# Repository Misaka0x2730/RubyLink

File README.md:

# RubyLink
Hardware platform for Miyako-Link based on RP2040

Firmware: https://github.com/Misaka0x2730/Miyako-Link

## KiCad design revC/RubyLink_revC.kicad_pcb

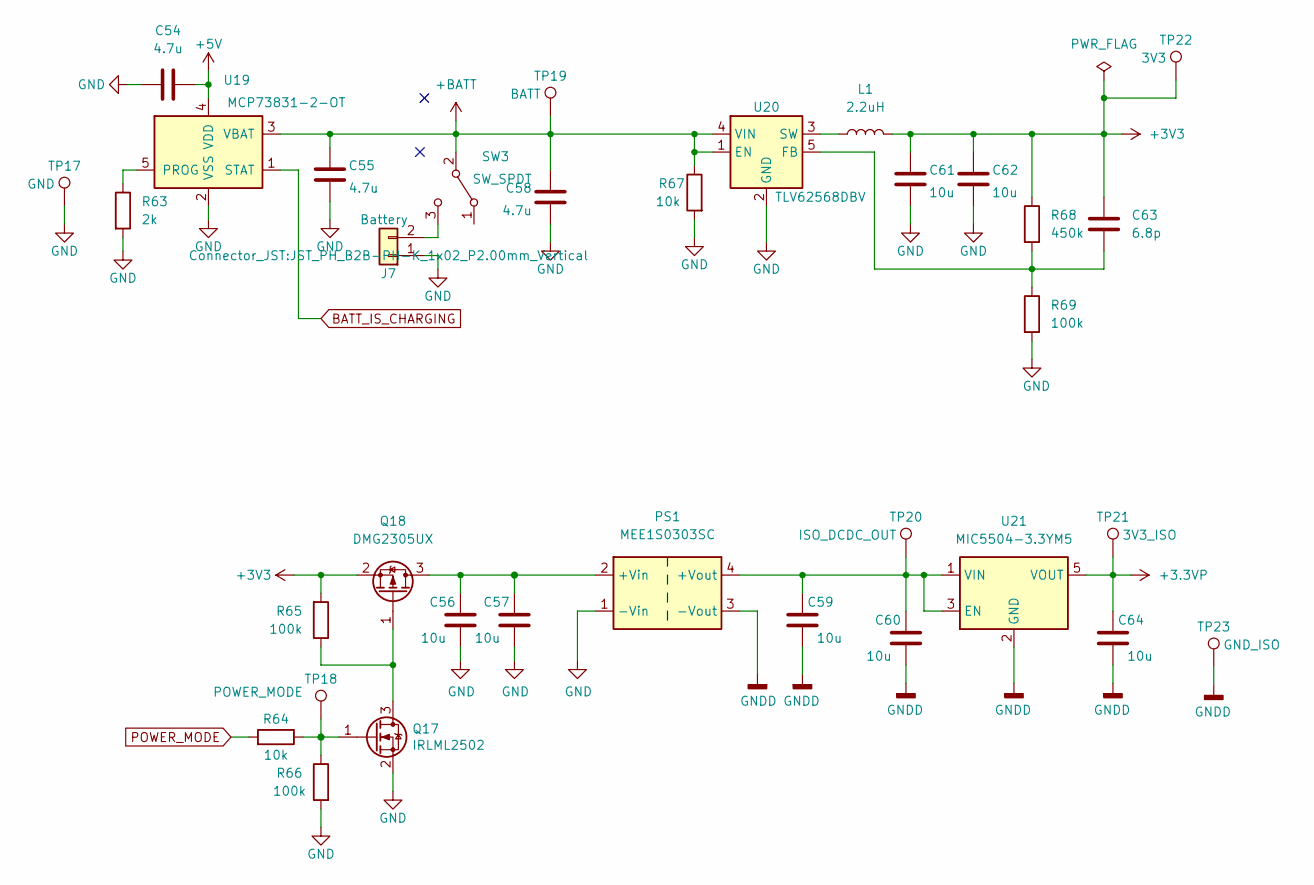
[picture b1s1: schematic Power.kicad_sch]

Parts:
C54, C55, C58: 4.7u; C_0603_1608Metric
C56, C57, C59, C60, C64: 10u; C_0603_1608Metric; Part Number CC0603KRX5R6BB106
C61, C62: 10u; C_0603_1608Metric
C63: 6.8p; C_0402_1005Metric
J7: Battery; JST_PH_B2B-PH-K_1x02_P2.00mm_Vertical
L1: 2.2uH; L_Taiyo-Yuden_NR-30xx; Part number NR3012T2R2M
PS1: MEE1S0303SC; Converter_DCDC_Murata_MEE1SxxxxSC_THT
Q17: IRLML2502; SOT-23; Part Number IRLML2502TRPBF
Q18: DMG2305UX; SOT-23
R63: 2k; R_0402_1005Metric
R64, R67: 10k; R_0402_1005Metric
R65, R69: 100k; R_0402_1005Metric
R66: 100k; R_0402_1005Metric; Part Number RC0402FR-0710KL
R68: 450k; R_0402_1005Metric
SW3: SW_SPDT; SW_CuK_OS102011MA1QN1_SPDT_Angled
TP17: GND; TestPoint_Pad_D1.0mm
TP18: POWER_MODE; TestPoint_Pad_D1.0mm
TP19: BATT; TestPoint_Pad_D1.0mm
TP20: ISO_DCDC_OUT; TestPoint_Pad_D1.0mm
TP21: 3V3_ISO; TestPoint_Pad_D1.0mm
TP22: 3V3; TestPoint_Pad_D1.0mm
TP23: GND_ISO; TestPoint_Pad_D1.0mm
U19: MCP73831-2-OT; SOT-23-5
U20: TLV62568DBV; SOT-23-5
U21: MIC5504-3.3YM5; SOT-23-5

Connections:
+3.3VP: C64.1, TP21.1, U21.5 (VOUT); also elsewhere on the board
+3V3: C61.1, C62.1, C63.1, L1.2, Q18.2 (S), R65.2, R68.1, TP22.1; also elsewhere on the board
+5V: C54.1, U19.4 (VDD); also elsewhere on the board
+BATT: C55.2, C58.2, R67.1, SW3.2 (B), TP19.1, U19.3 (VBAT), U20.1 (EN), U20.4 (VIN)
BATT_IS_CHARGING: U19.1 (STAT); also elsewhere on the board
GND: C54.2, C55.1, C56.2, C57.2, C58.1, C61.2, C62.2, J7.1, PS1.1 (-Vin), Q17.2 (S), R63.2, R66.2, R67.2, R69.2, TP17.1, U19.2 (VSS), U20.2 (GND); also elsewhere on the board
GNDD: C59.2, C60.2, C64.2, PS1.3 (-Vout), TP23.1, U21.2 (GND); also elsewhere on the board
unnamed: C56.1, C57.1, PS1.2 (+Vin), Q18.3 (D)
unnamed: C59.1, C60.1, PS1.4 (+Vout), TP20.1, U21.1 (VIN), U21.3 (EN)
unnamed: C63.2, R68.2, R69.1, U20.5 (FB)
unnamed: J7.2, SW3.3 (C)
unnamed: L1.1, U20.3 (SW)
unnamed: Q17.1 (G), R64.1, R66.1, TP18.1
unnamed: Q17.3 (D), Q18.1 (G), R65.1
unnamed: R63.1, U19.5 (PROG)
POWER_MODE: R64.2; also elsewhere on the board

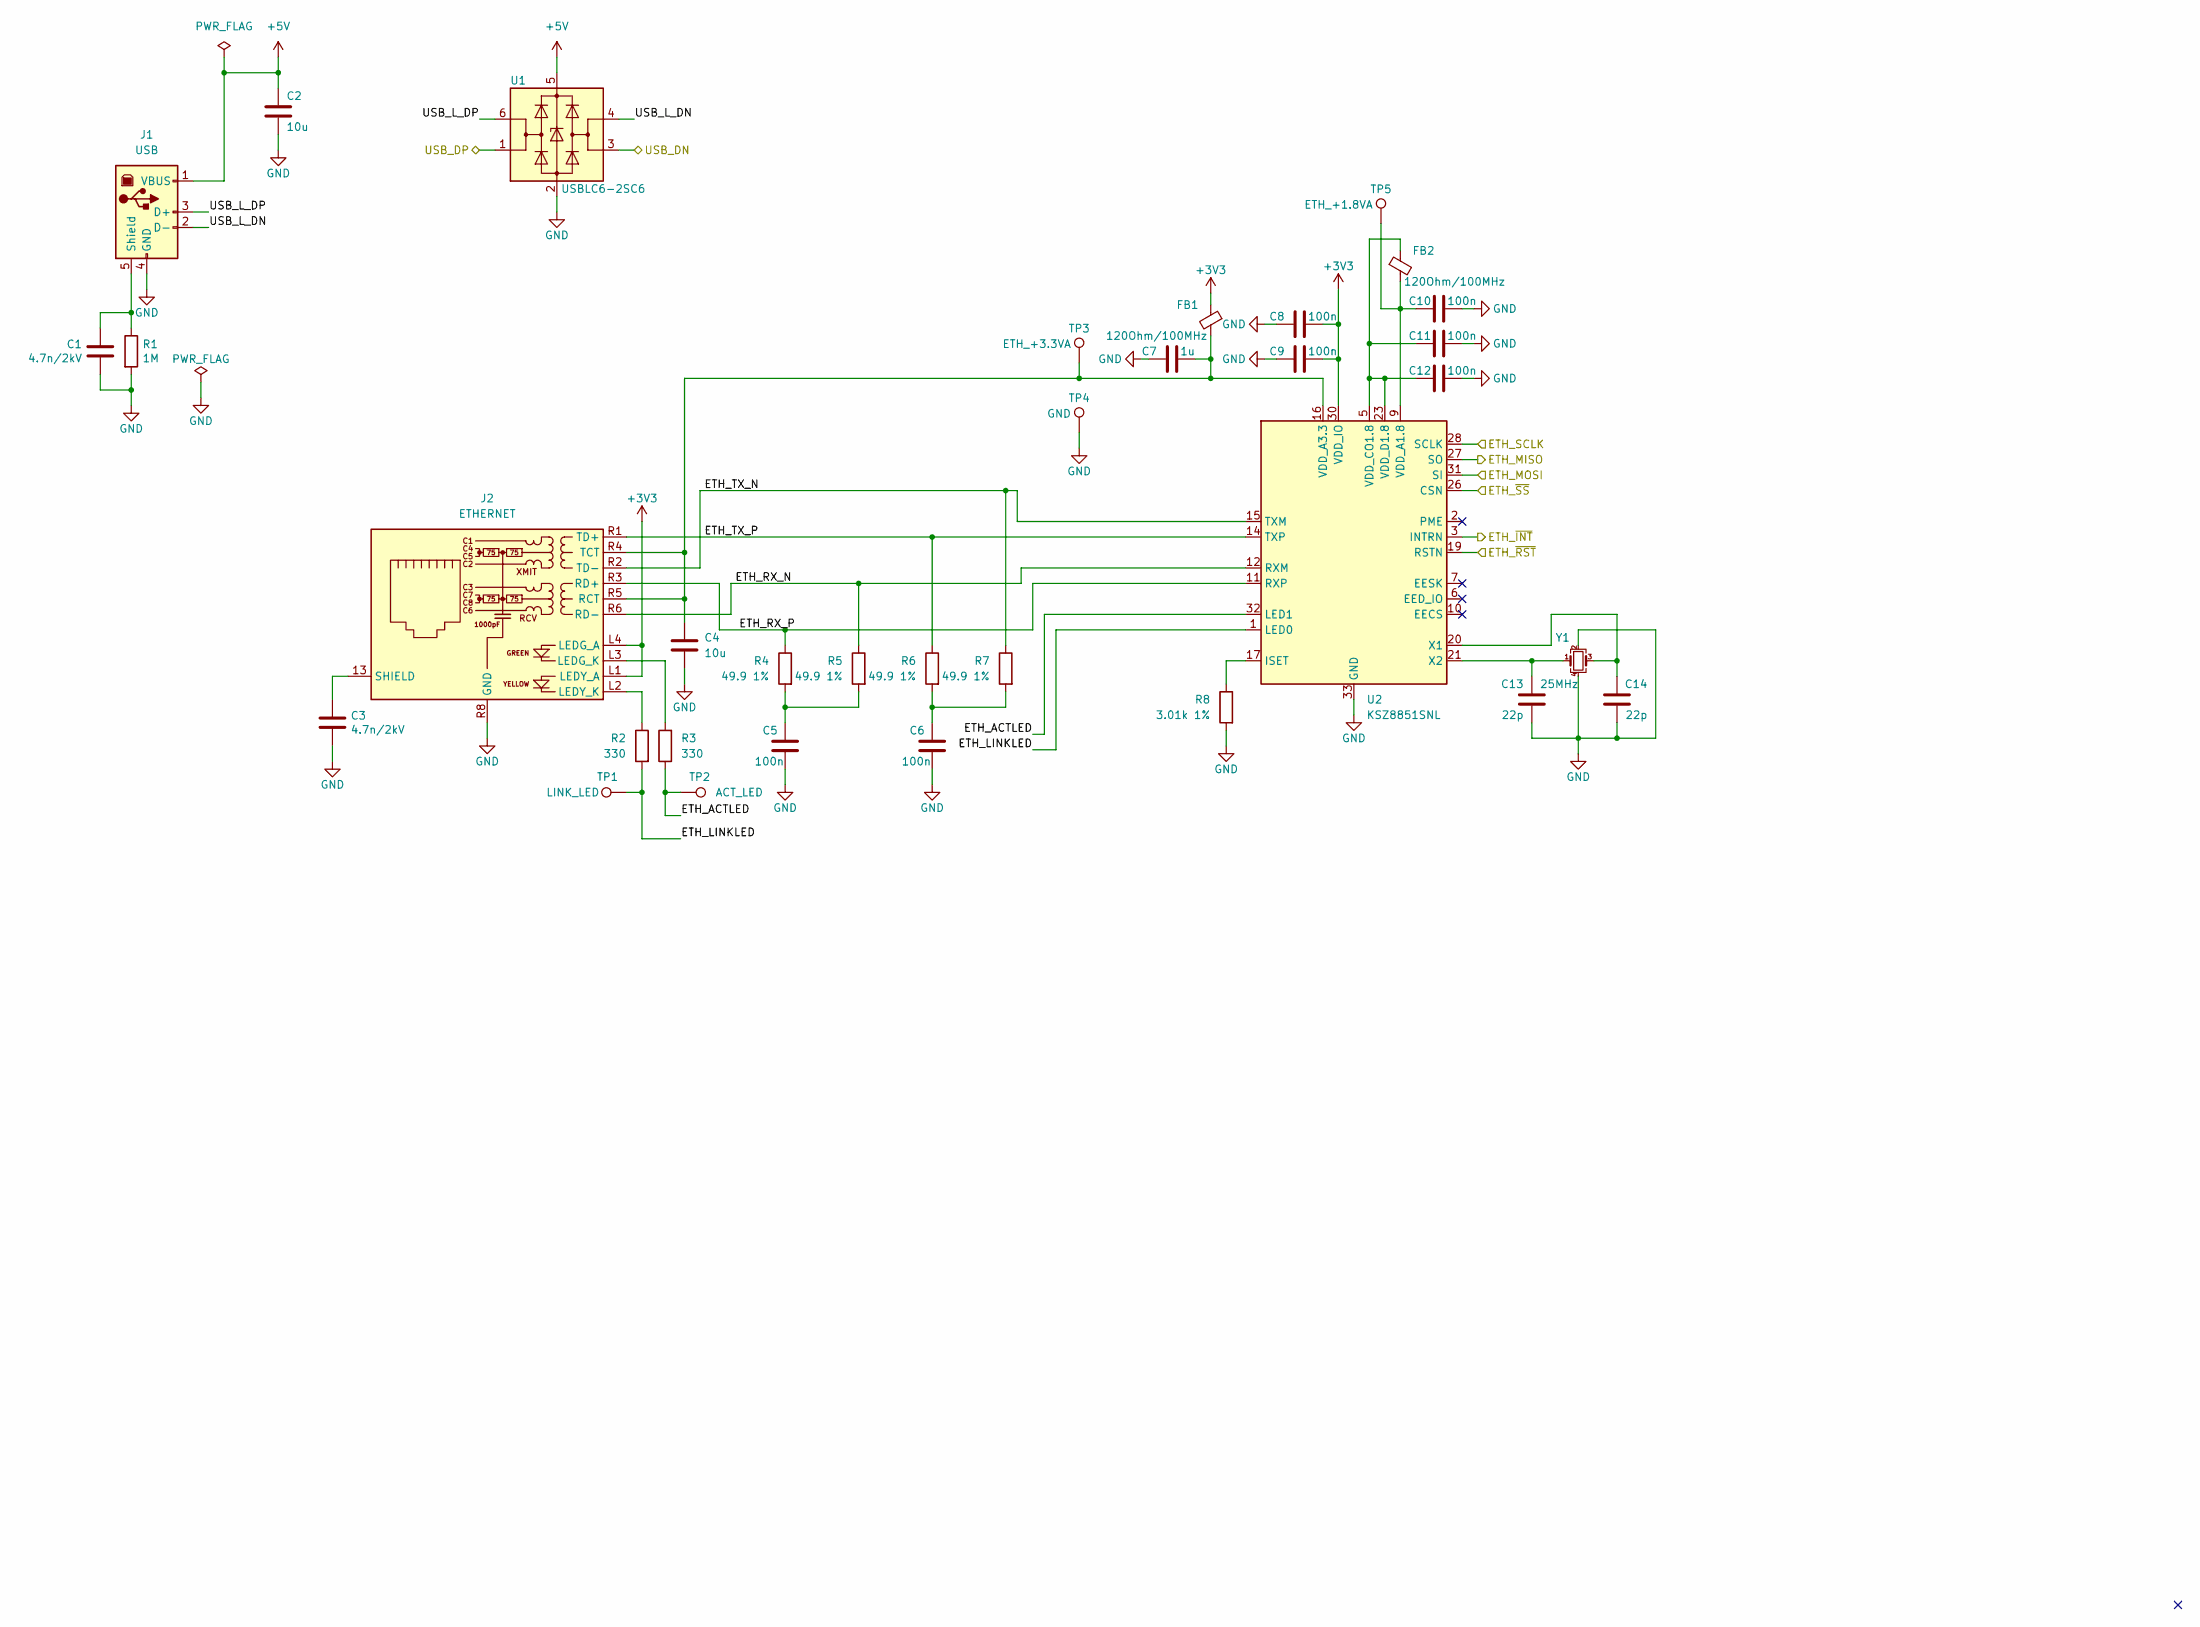
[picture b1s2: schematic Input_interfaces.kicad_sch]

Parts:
C1, C3: 4.7n/2kV; C_1812_4532Metric; Part Number 202S43W472KV4E
C2, C4: 10u; C_0603_1608Metric
C5, C6, C8, C9, C10, C11, C12: 100n; C_0402_1005Metric
C7: 1u; C_0402_1005Metric
C13, C14: 22p; C_0402_1005Metric
FB1, FB2: 120Ohm/100MHz; L_0805_2012Metric
J1: USB; TE_292304-2
J2: ETHERNET; RJ45_Amphenol_RJMG1BD3B8K1ANR
R1: 1M; R_1206_3216Metric; Part Number 1206W4J0105T5E
R2, R3: 330; R_0402_1005Metric
R4, R5, R6, R7: 49.9 1%; R_0603_1608Metric
R8: 3.01k 1%; R_0402_1005Metric
TP1: LINK_LED; TestPoint_Pad_D1.0mm
TP2: ACT_LED; TestPoint_Pad_D1.0mm
TP3: ETH_+3.3VA; TestPoint_Pad_D1.0mm
TP4: GND; TestPoint_Pad_D1.0mm
TP5: ETH_+1.8VA; TestPoint_Pad_D1.0mm
U1: USBLC6-2SC6; SOT-23-6
U2: KSZ8851SNL; TQFN-32-1EP_5x5mm_P0.5mm_EP3.4x3.4mm_ThermalVias
Y1: 25MHz; Crystal_SMD_3225-4Pin_3.2x2.5mm

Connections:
+3V3: C8.2, C9.2, FB1.1, J2.L1 (LEDY_A), J2.L4 (LEDG_A), U2.25 (VDD_IO), U2.30 (VDD_IO); also elsewhere on the board
+5V: C2.1, J1.1 (VBUS), U1.5 (VBUS); also elsewhere on the board
/Input interfaces/ETH_ACTLED: R3.1, TP2.1, U2.32 (LED1)
/Input interfaces/ETH_LINKLED: R2.2, TP1.1, U2.1 (LED0)
/Input interfaces/ETH_MISO: U2.27 (SO); also elsewhere on the board
/Input interfaces/ETH_MOSI: U2.31 (SI); also elsewhere on the board
/Input interfaces/ETH_RX_N: J2.R6 (RD-), R5.1, U2.12 (RXM)
/Input interfaces/ETH_RX_P: J2.R3 (RD+), R4.1, U2.11 (RXP)
/Input interfaces/ETH_SCLK: U2.28 (SCLK); also elsewhere on the board
/Input interfaces/ETH_TX_N: J2.R2 (TD-), R7.1, U2.15 (TXM)
/Input interfaces/ETH_TX_P: J2.R1 (TD+), R6.1, U2.14 (TXP)
/Input interfaces/ETH_~INT: U2.3 (INTRN); also elsewhere on the board
/Input interfaces/ETH_~RST: U2.19 (RSTN); also elsewhere on the board
/Input interfaces/ETH_~SS: U2.26 (CSN); also elsewhere on the board
/Input interfaces/USB_DN: U1.3 (I/O2); also elsewhere on the board
/Input interfaces/USB_DP: U1.1 (I/O1); also elsewhere on the board
/Input interfaces/USB_L_DN: J1.2 (D-), U1.4 (I/O2)
/Input interfaces/USB_L_DP: J1.3 (D+), U1.6 (I/O1)
GND: C1.1, C2.2, C3.1, C4.1, C5.2, C6.2, C7.1, C8.1, C9.1, C10.2, C11.2, C12.2, C13.2, C14.2, J1.4 (GND), J2.R8 (GND), R1.2, R8.2, TP4.1, U1.2 (GND), U2.4 (DGND), U2.8 (AGND), U2.13 (AGND), U2.18 (AGND), U2.22 (DGND), U2.24 (DGND), U2.29 (DGND), U2.33 (GND), Y1.2, Y1.4; also elsewhere on the board
unnamed: C1.2, J1.5 (Shield), R1.1
unnamed: C3.2, J2.13 (SHIELD)
unnamed: C4.2, C7.2, FB1.2, J2.R4 (TCT), J2.R5 (RCT), TP3.1, U2.16 (VDD_A3.3)
unnamed: C5.1, R4.2, R5.2
unnamed: C6.1, R6.2, R7.2
unnamed: C10.1, FB2.2, TP5.1, U2.9 (VDD_A1.8)
unnamed: C11.1, C12.1, FB2.1, U2.5 (VDD_CO1.8), U2.23 (VDD_D1.8)
unnamed: C13.1, U2.21 (X2), Y1.1
unnamed: C14.1, U2.20 (X1), Y1.3
unnamed: J2.L2 (LEDY_K), R2.1
unnamed: J2.L3 (LEDG_K), R3.2
unnamed: R8.1, U2.17 (ISET)

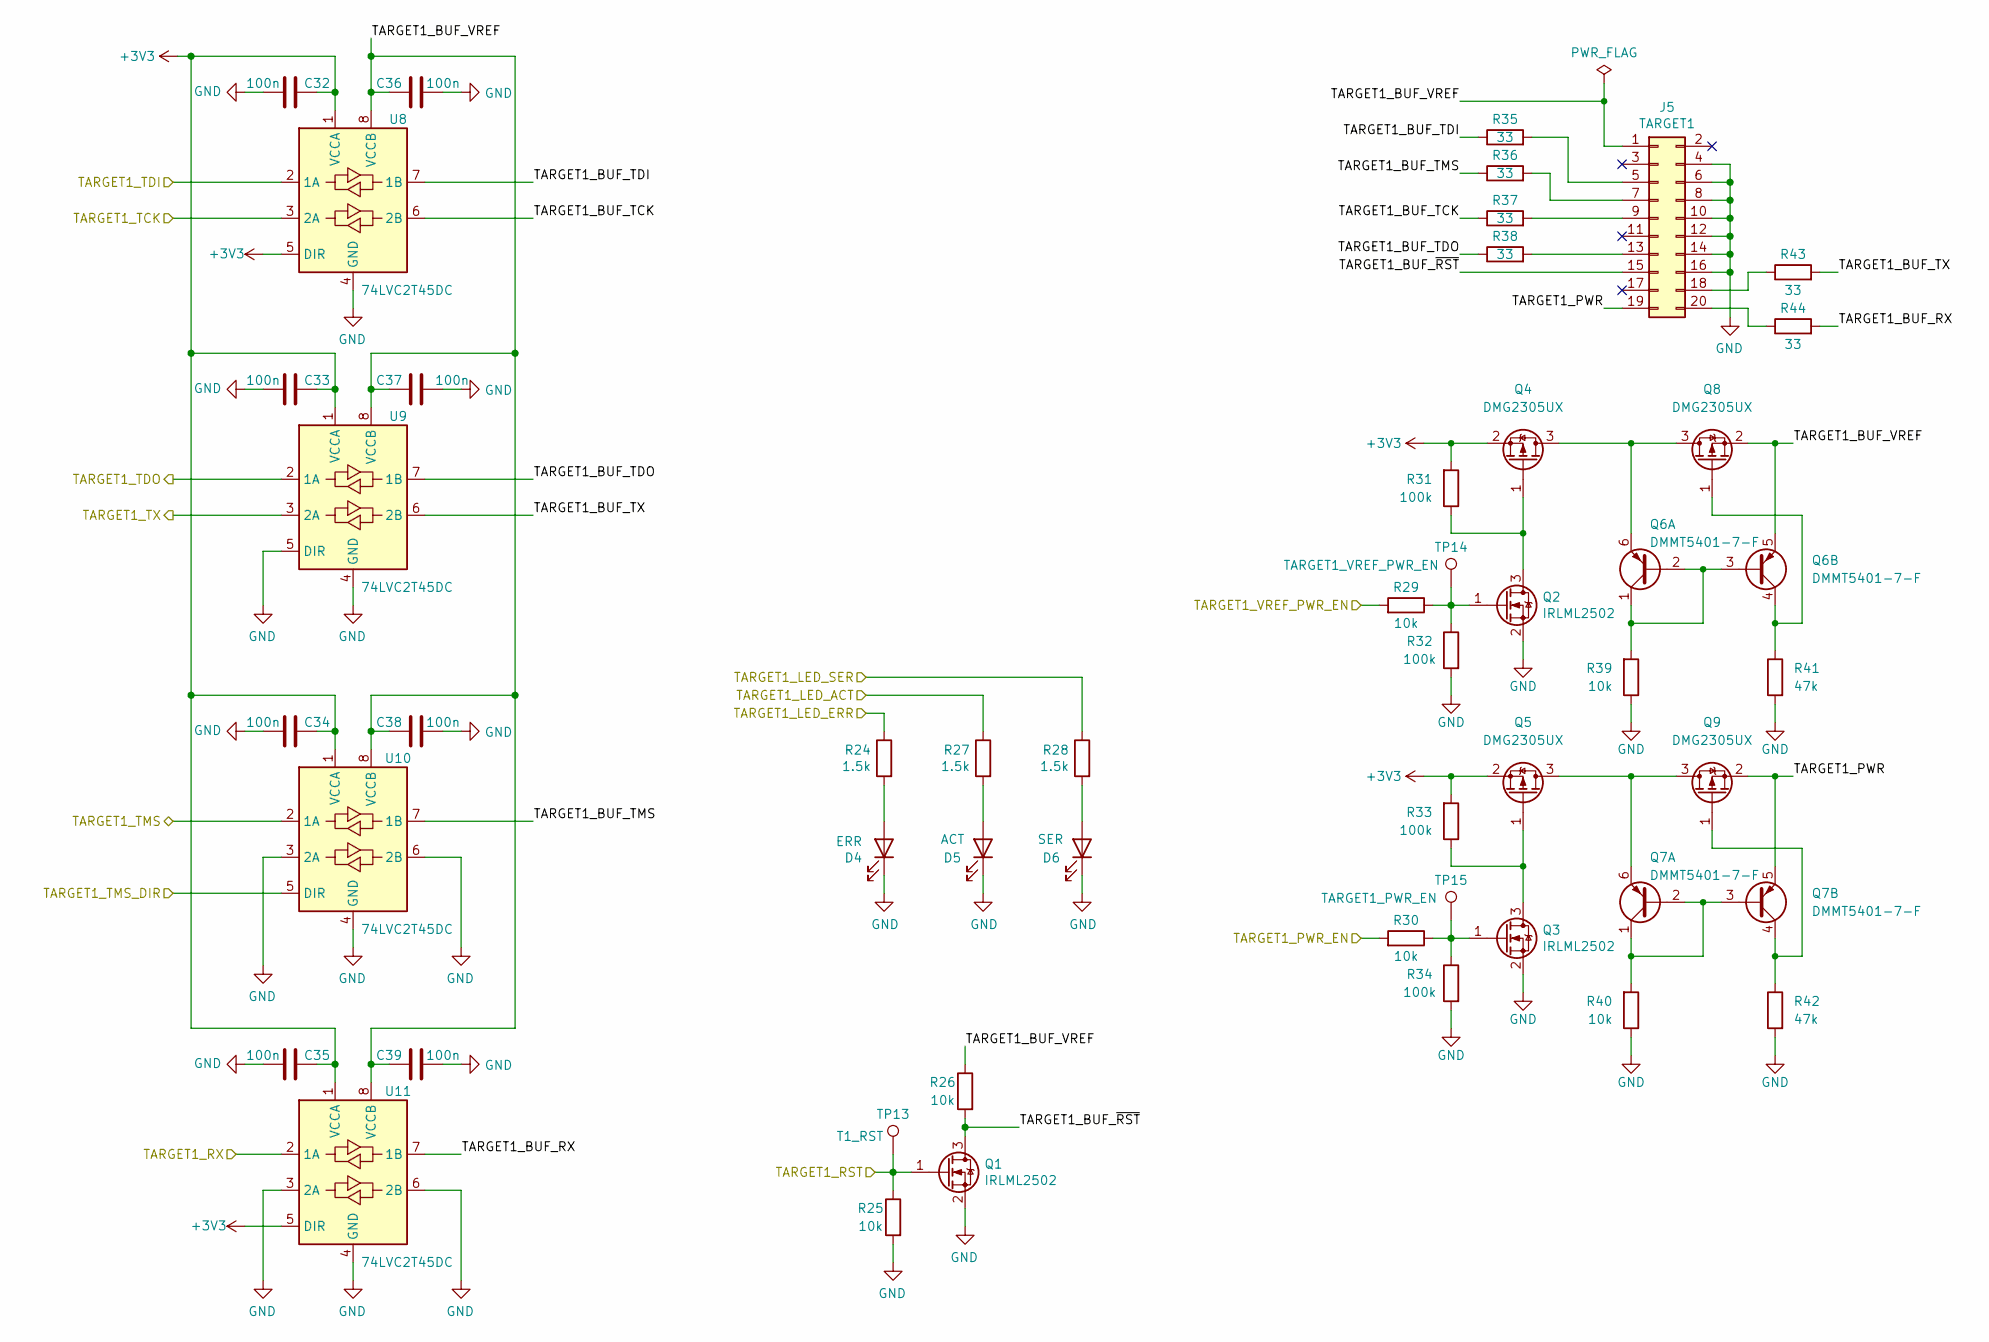
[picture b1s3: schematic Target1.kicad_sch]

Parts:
C32, C33, C34, C35, C36, C37, C38, C39: 100n; C_0402_1005Metric; Part Number CC0402KRX7R7BB104
D4: ERR; LED_D3.0mm
D5: ACT; LED_D3.0mm
D6: SER; LED_D3.0mm; Part Number FYLS-0603UYC
J5: TARGET1; IDC-Header_2x10_P2.54mm_Horizontal; Part Number BH-20R
Q1, Q2, Q3: IRLML2502; SOT-23; Part Number IRLML2502TRPBF
Q4, Q5, Q8, Q9: DMG2305UX; SOT-23
Q6, Q7: DMMT5401-7-F; SOT-23-6
R24, R27, R28: 1.5k; R_0603_1608Metric; Part Number RC0402FR-071K5L
R25, R26: 10k; R_0402_1005Metric; Part Number RC0402FR-0710KL
R29, R30, R39, R40: 10k; R_0402_1005Metric
R31, R33: 100k; R_0402_1005Metric
R32, R34: 100k; R_0402_1005Metric; Part Number RC0402FR-0710KL
R35, R36, R37, R38, R43, R44: 33; R_0402_1005Metric; Part Number RC0402FR-07100KL
R41, R42: 47k; R_0402_1005Metric
TP13: T1_RST; TestPoint_Pad_D1.0mm
TP14: TARGET1_VREF_PWR_EN; TestPoint_Pad_D1.0mm
TP15: TARGET1_PWR_EN; TestPoint_Pad_D1.0mm
U8, U9, U10, U11: 74LVC2T45DC; VSSOP-8_2.3x2mm_P0.5mm; Part Number SN74LVC2T45DCUR

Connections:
+3V3: C32.1, C33.1, C34.1, C35.1, Q4.2 (S), Q5.2 (S), R31.2, R33.2, U8.1 (VCCA), U8.5 (DIR), U9.1 (VCCA), U10.1 (VCCA), U11.1 (VCCA), U11.5 (DIR); also elsewhere on the board
/MCU/TARGET1_LED_ACT: R27.1; also elsewhere on the board
/MCU/TARGET1_LED_ERR: R24.1; also elsewhere on the board
/MCU/TARGET1_LED_SER: R28.1; also elsewhere on the board
/MCU/TARGET1_PWR_EN: R30.2; also elsewhere on the board
/MCU/TARGET1_RST: Q1.1 (G), R25.1, TP13.1; also elsewhere on the board
/MCU/TARGET1_RX: U9.3 (2A); also elsewhere on the board
/MCU/TARGET1_TCK: U8.3 (2A); also elsewhere on the board
/MCU/TARGET1_TDI: U8.2 (1A); also elsewhere on the board
/MCU/TARGET1_TDO: U9.2 (1A); also elsewhere on the board
/MCU/TARGET1_TMS: U10.2 (1A); also elsewhere on the board
/MCU/TARGET1_TMS_DIR: U10.5 (DIR); also elsewhere on the board
/MCU/TARGET1_TX: U11.2 (1A); also elsewhere on the board
/MCU/TARGET1_VREF_PWR_EN: R29.2; also elsewhere on the board
/Target1/TARGET1_BUF_RX: R44.2, U11.7 (1B)
/Target1/TARGET1_BUF_TCK: R37.1, U8.6 (2B)
/Target1/TARGET1_BUF_TDI: R35.1, U8.7 (1B)
/Target1/TARGET1_BUF_TDO: R38.1, U9.7 (1B)
/Target1/TARGET1_BUF_TMS: R36.1, U10.7 (1B)
/Target1/TARGET1_BUF_TX: R43.2, U9.6 (2B)
/Target1/TARGET1_BUF_VREF: C36.2, C37.2, C38.2, C39.2, J5.1, Q6.5 (E2), Q8.2 (S), R26.1, U8.8 (VCCB), U9.8 (VCCB), U10.8 (VCCB), U11.8 (VCCB)
/Target1/TARGET1_BUF_~RST: J5.15, Q1.3 (D), R26.2
/Target1/TARGET1_PWR: J5.19, Q7.5 (E2), Q9.2 (S)
GND: C32.2, C33.2, C34.2, C35.2, C36.1, C37.1, C38.1, C39.1, D4.1 (K), D5.1 (K), D6.1 (K), J5.4, J5.6, J5.8, J5.10, J5.12, J5.14, J5.16, Q1.2 (S), Q2.2 (S), Q3.2 (S), R25.2, R32.2, R34.2, R39.1, R40.1, R41.2, R42.2, U8.4 (GND), U9.4 (GND), U9.5 (DIR), U10.3 (2A), U10.4 (GND), U10.6 (2B), U11.3 (2A), U11.4 (GND), U11.6 (2B); also elsewhere on the board
unnamed: D4.2 (A), R24.2
unnamed: D5.2 (A), R27.2
unnamed: D6.2 (A), R28.2
unnamed: J5.5, R35.2
unnamed: J5.7, R36.2
unnamed: J5.9, R37.2
unnamed: J5.13, R38.2
unnamed: J5.18, R43.1
unnamed: J5.20, R44.1
unnamed: Q2.1 (G), R29.1, R32.1, TP14.1
unnamed: Q2.3 (D), Q4.1 (G), R31.1
unnamed: Q3.1 (G), R30.1, R34.1, TP15.1
unnamed: Q3.3 (D), Q5.1 (G), R33.1
unnamed: Q4.3 (D), Q6.6 (E1), Q8.3 (D)
unnamed: Q5.3 (D), Q7.6 (E1), Q9.3 (D)
unnamed: Q6.1 (C1), Q6.2 (B1), Q6.3 (B2), R39.2
unnamed: Q6.4 (C2), Q8.1 (G), R41.1
unnamed: Q7.1 (C1), Q7.2 (B1), Q7.3 (B2), R40.2
unnamed: Q7.4 (C2), Q9.1 (G), R42.1

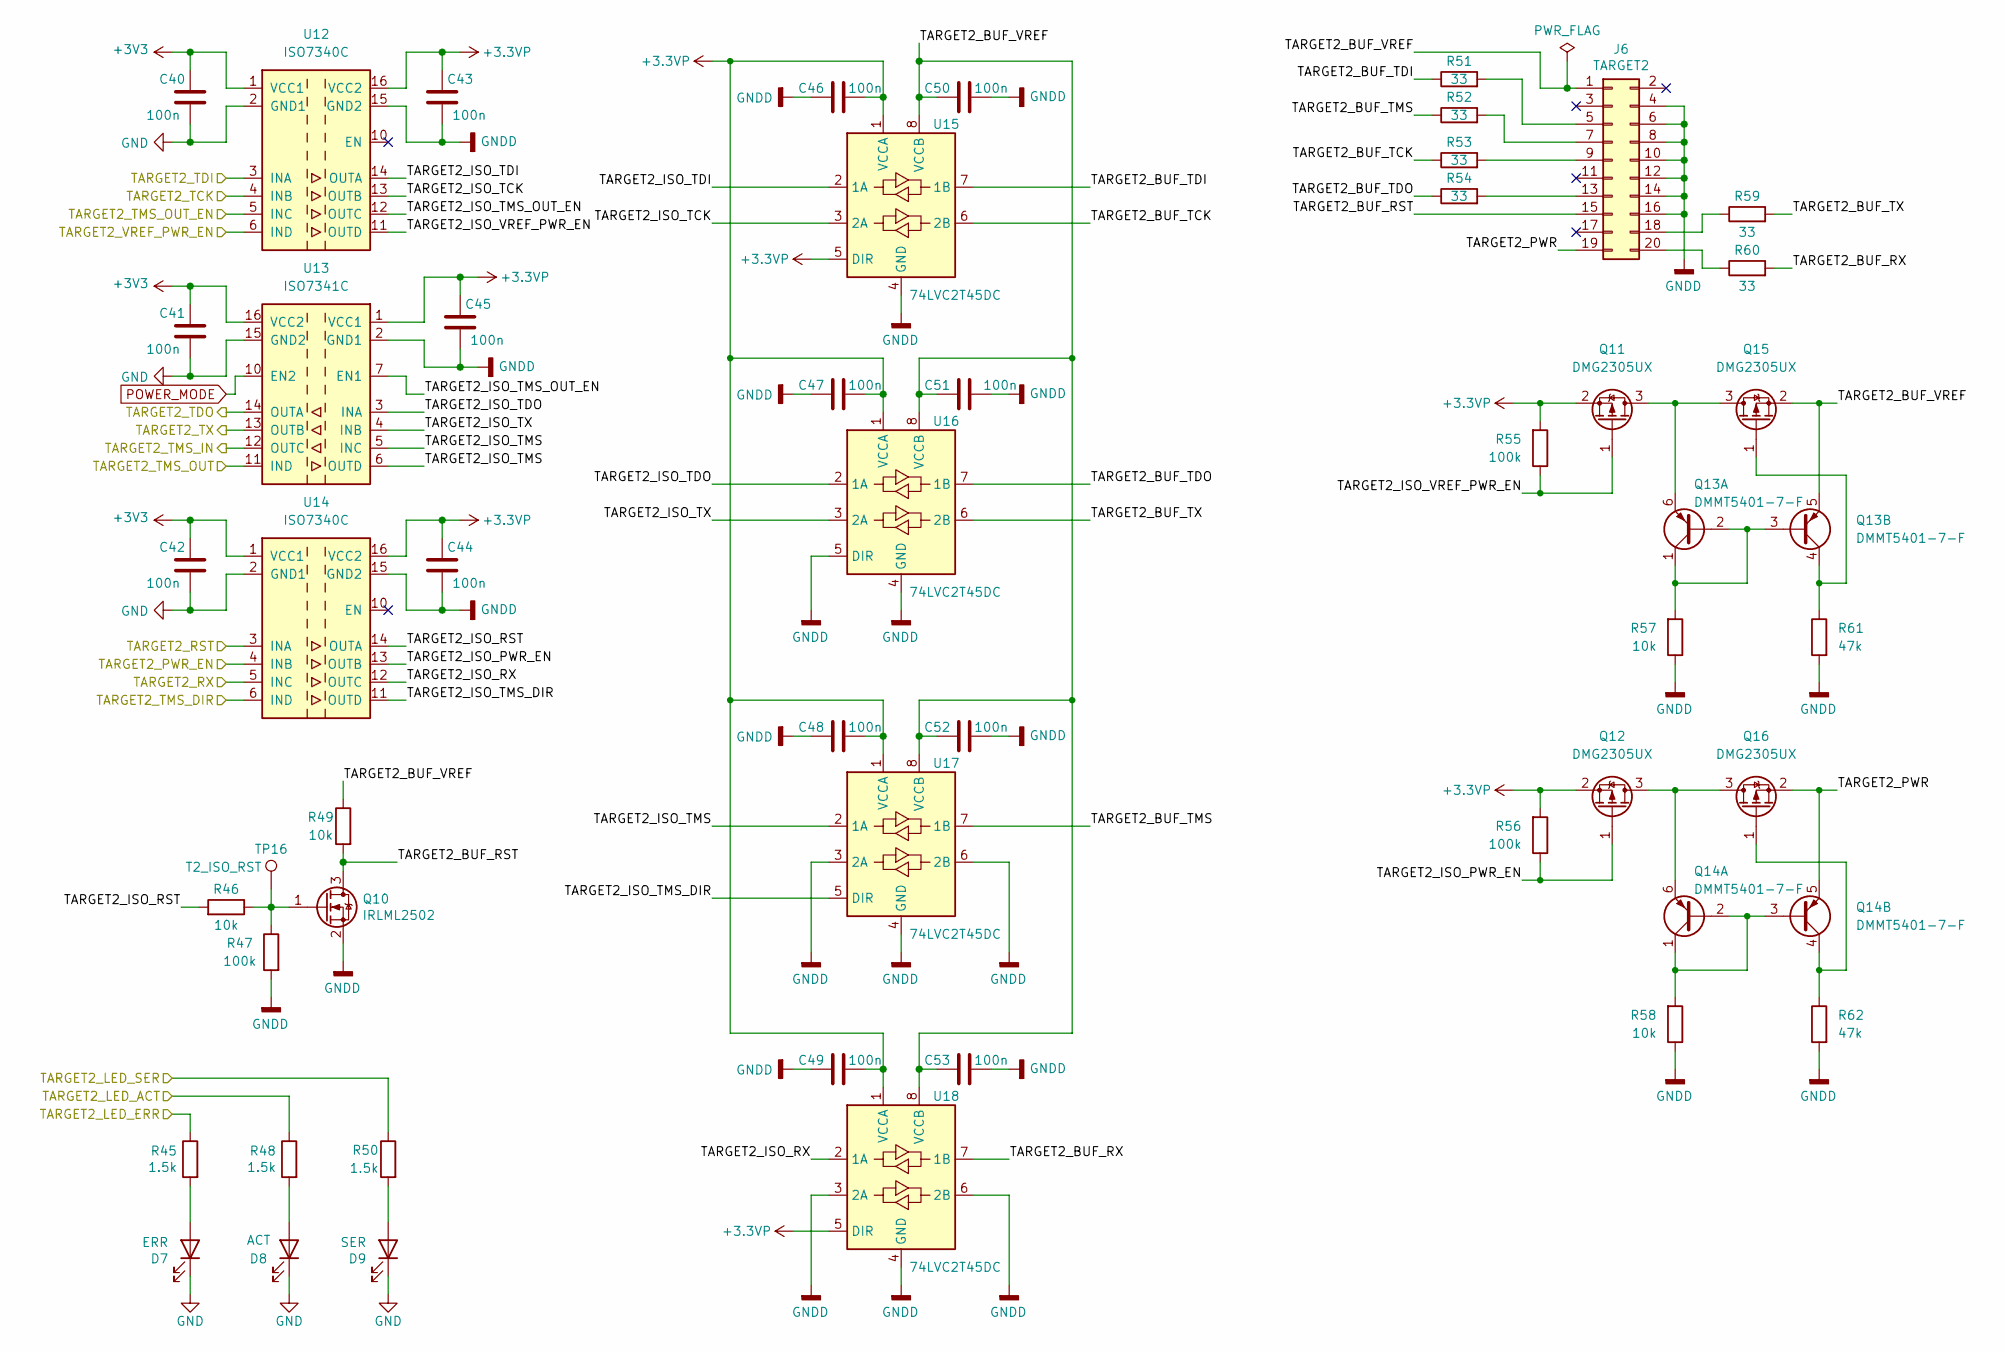
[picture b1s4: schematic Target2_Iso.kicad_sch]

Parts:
C40, C41, C42, C43, C44, C45, C46, C47, C48, C49, C50, C51, C52, C53: 100n; C_0402_1005Metric; Part Number CC0402KRX7R7BB104
D7: ERR; LED_D3.0mm
D8: ACT; LED_D3.0mm
D9: SER; LED_D3.0mm; Part Number FYLS-0603UYC
J6: TARGET2; IDC-Header_2x10_P2.54mm_Horizontal; Part Number BH-20R
Q10: IRLML2502; SOT-23; Part Number IRLML2502TRPBF
Q11, Q12, Q15, Q16: DMG2305UX; SOT-23
Q13, Q14: DMMT5401-7-F; SOT-23-6
R45, R48, R50: 1.5k; R_0603_1608Metric; Part Number RC0402FR-071K5L
R46, R57, R58: 10k; R_0402_1005Metric
R47: 100k; R_0402_1005Metric; Part Number RC0402FR-0710KL
R49: 10k; R_0402_1005Metric; Part Number RC0402FR-0710KL
R51, R52, R53, R54, R59, R60: 33; R_0402_1005Metric; Part Number RC0402FR-07100KL
R55, R56: 100k; R_0402_1005Metric
R61, R62: 47k; R_0402_1005Metric
TP16: T2_ISO_RST; TestPoint_Pad_D1.0mm
U12, U14: ISO7340C; SOIC-16W_7.5x10.3mm_P1.27mm
U13: ISO7341C; SOIC-16W_7.5x10.3mm_P1.27mm
U15, U16, U17, U18: 74LVC2T45DC; VSSOP-8_2.3x2mm_P0.5mm; Part Number SN74LVC2T45DCUR

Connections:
+3.3VP: C43.2, C44.2, C45.2, C46.2, C47.2, C48.2, C49.2, Q11.2 (S), Q12.2 (S), R55.2, R56.2, U12.16 (VCC2), U13.1 (VCC1), U14.16 (VCC2), U15.1 (VCCA), U15.5 (DIR), U16.1 (VCCA), U17.1 (VCCA), U18.1 (VCCA), U18.5 (DIR); also elsewhere on the board
+3V3: C40.2, C41.2, C42.2, U12.1 (VCC1), U13.16 (VCC2), U14.1 (VCC1); also elsewhere on the board
/MCU/TARGET2_LED_ACT: R48.1; also elsewhere on the board
/MCU/TARGET2_LED_ERR: R45.1; also elsewhere on the board
/MCU/TARGET2_LED_SER: R50.1; also elsewhere on the board
/MCU/TARGET2_PWR_EN: U14.4 (INB); also elsewhere on the board
/MCU/TARGET2_RST: U14.3 (INA); also elsewhere on the board
/MCU/TARGET2_RX: U13.13 (OUTB); also elsewhere on the board
/MCU/TARGET2_TCK: U12.4 (INB); also elsewhere on the board
/MCU/TARGET2_TDI: U12.3 (INA); also elsewhere on the board
/MCU/TARGET2_TDO: U13.14 (OUTA); also elsewhere on the board
/MCU/TARGET2_TMS_DIR: U14.6 (IND); also elsewhere on the board
/MCU/TARGET2_TMS_IN: U13.12 (OUTC); also elsewhere on the board
/MCU/TARGET2_TMS_OUT: U13.11 (IND); also elsewhere on the board
/MCU/TARGET2_TMS_OUT_EN: U12.5 (INC); also elsewhere on the board
/MCU/TARGET2_TX: U14.5 (INC); also elsewhere on the board
/MCU/TARGET2_VREF_PWR_EN: U12.6 (IND); also elsewhere on the board
/Target2_Iso/TARGET2_BUF_RST: J6.15, Q10.3 (D), R49.2
/Target2_Iso/TARGET2_BUF_RX: R60.2, U18.7 (1B)
/Target2_Iso/TARGET2_BUF_TCK: R53.1, U15.6 (2B)
/Target2_Iso/TARGET2_BUF_TDI: R51.1, U15.7 (1B)
/Target2_Iso/TARGET2_BUF_TDO: R54.1, U16.7 (1B)
/Target2_Iso/TARGET2_BUF_TMS: R52.1, U17.7 (1B)
/Target2_Iso/TARGET2_BUF_TX: R59.2, U16.6 (2B)
/Target2_Iso/TARGET2_BUF_VREF: C50.2, C51.2, C52.2, C53.2, J6.1, Q13.5 (E2), Q15.2 (S), R49.1, U15.8 (VCCB), U16.8 (VCCB), U17.8 (VCCB), U18.8 (VCCB)
/Target2_Iso/TARGET2_ISO_PWR_EN: Q12.1 (G), R56.1, U14.13 (OUTB)
/Target2_Iso/TARGET2_ISO_RST: R46.2, U14.14 (OUTA)
/Target2_Iso/TARGET2_ISO_RX: U14.12 (OUTC), U18.2 (1A)
/Target2_Iso/TARGET2_ISO_TCK: U12.13 (OUTB), U15.3 (2A)
/Target2_Iso/TARGET2_ISO_TDI: U12.14 (OUTA), U15.2 (1A)
/Target2_Iso/TARGET2_ISO_TDO: U13.3 (INA), U16.2 (1A)
/Target2_Iso/TARGET2_ISO_TMS: U13.5 (INC), U13.6 (OUTD), U17.2 (1A)
/Target2_Iso/TARGET2_ISO_TMS_DIR: U14.11 (OUTD), U17.5 (DIR)
/Target2_Iso/TARGET2_ISO_TMS_OUT_EN: U12.12 (OUTC), U13.7 (EN1)
/Target2_Iso/TARGET2_ISO_TX: U13.4 (INB), U16.3 (2A)
/Target2_Iso/TARGET2_ISO_VREF_PWR_EN: Q11.1 (G), R55.1, U12.11 (OUTD)
/Target2_Iso/TARGET2_PWR: J6.19, Q14.5 (E2), Q16.2 (S)
GND: C40.1, C41.1, C42.1, D7.1 (K), D8.1 (K), D9.1 (K), U12.2 (GND1), U12.8 (GND1), U13.9 (GND2), U13.15 (GND2), U14.2 (GND1), U14.8 (GND1); also elsewhere on the board
GNDD: C43.1, C44.1, C45.1, C46.1, C47.1, C48.1, C49.1, C50.1, C51.1, C52.1, C53.1, J6.4, J6.6, J6.8, J6.10, J6.12, J6.14, J6.16, Q10.2 (S), R47.2, R57.1, R58.1, R61.2, R62.2, U12.9 (GND2), U12.15 (GND2), U13.2 (GND1), U13.8 (GND1), U14.9 (GND2), U14.15 (GND2), U15.4 (GND), U16.4 (GND), U16.5 (DIR), U17.3 (2A), U17.4 (GND), U17.6 (2B), U18.3 (2A), U18.4 (GND), U18.6 (2B); also elsewhere on the board
unnamed: D7.2 (A), R45.2
unnamed: D8.2 (A), R48.2
unnamed: D9.2 (A), R50.2
unnamed: J6.5, R51.2
unnamed: J6.7, R52.2
unnamed: J6.9, R53.2
unnamed: J6.13, R54.2
unnamed: J6.18, R59.1
unnamed: J6.20, R60.1
unnamed: Q10.1 (G), R46.1, R47.1, TP16.1
unnamed: Q11.3 (D), Q13.6 (E1), Q15.3 (D)
unnamed: Q12.3 (D), Q14.6 (E1), Q16.3 (D)
unnamed: Q13.1 (C1), Q13.2 (B1), Q13.3 (B2), R57.2
unnamed: Q13.4 (C2), Q15.1 (G), R61.1
unnamed: Q14.1 (C1), Q14.2 (B1), Q14.3 (B2), R58.2
unnamed: Q14.4 (C2), Q16.1 (G), R62.1
POWER_MODE: U13.10 (EN2); also elsewhere on the board
